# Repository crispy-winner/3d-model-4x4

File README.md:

# Macro Pad 4x4

В данном репозитории разведена печатная плата на основе микроконтроллера
[STM32F103CBT6](https://aliexpress.ru/popular/stm32f103cbt6.html) с USB Type-C.

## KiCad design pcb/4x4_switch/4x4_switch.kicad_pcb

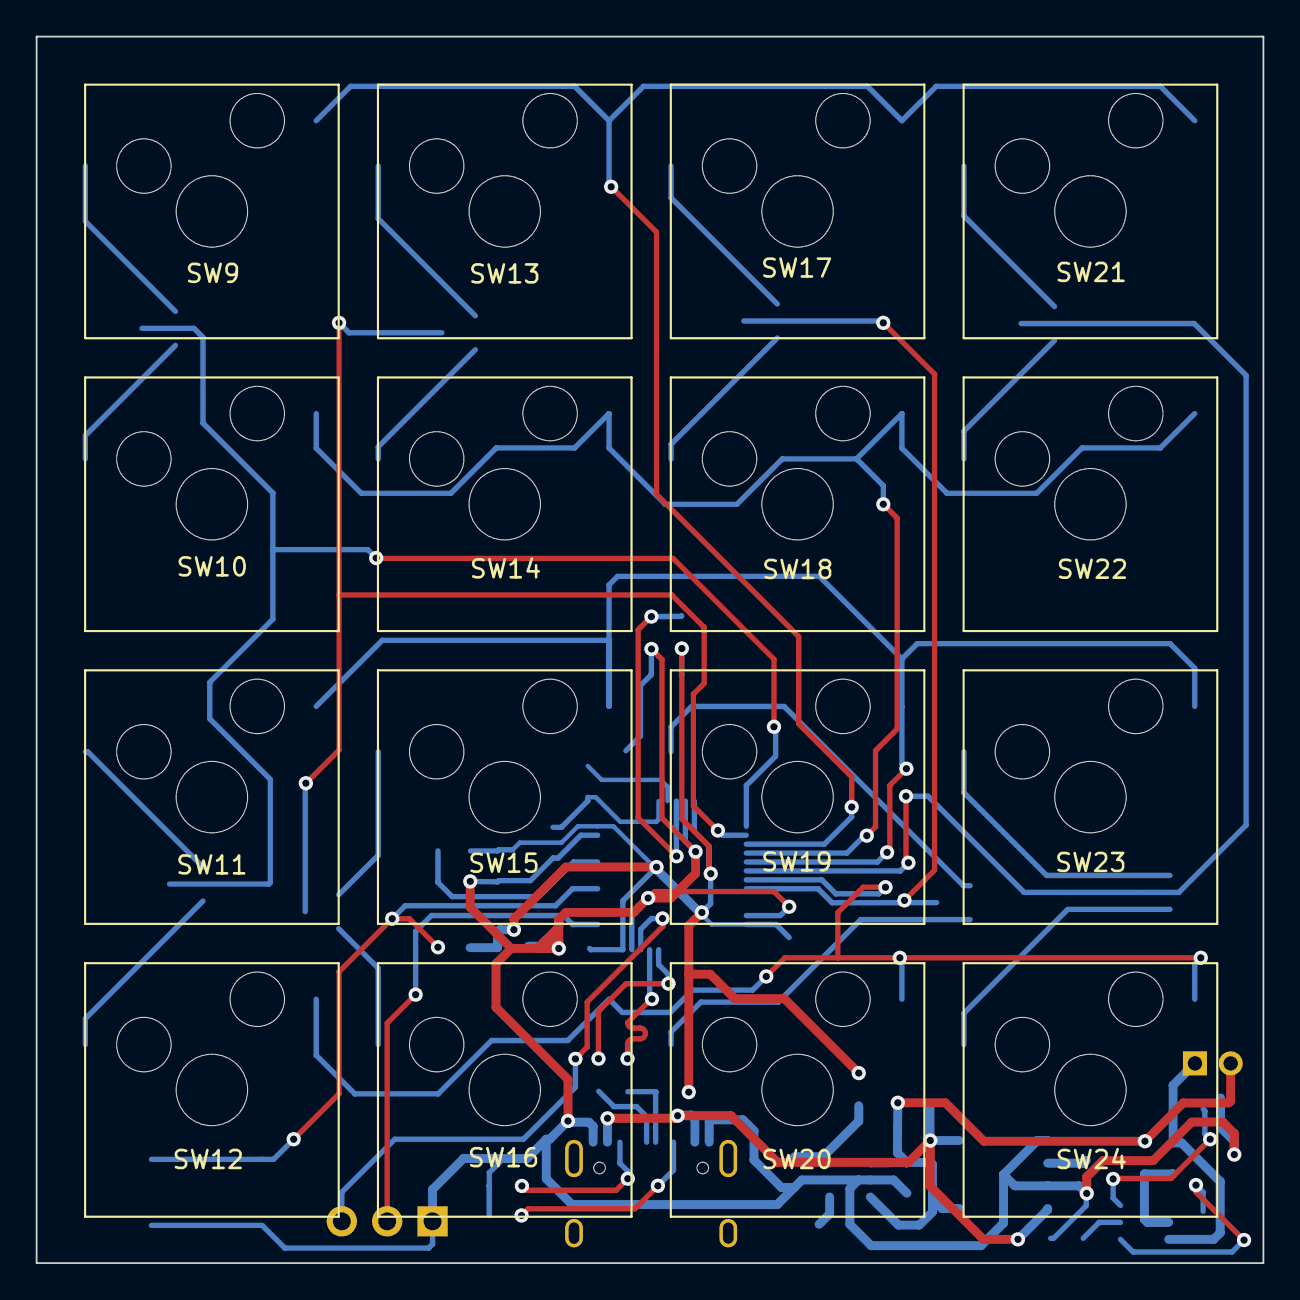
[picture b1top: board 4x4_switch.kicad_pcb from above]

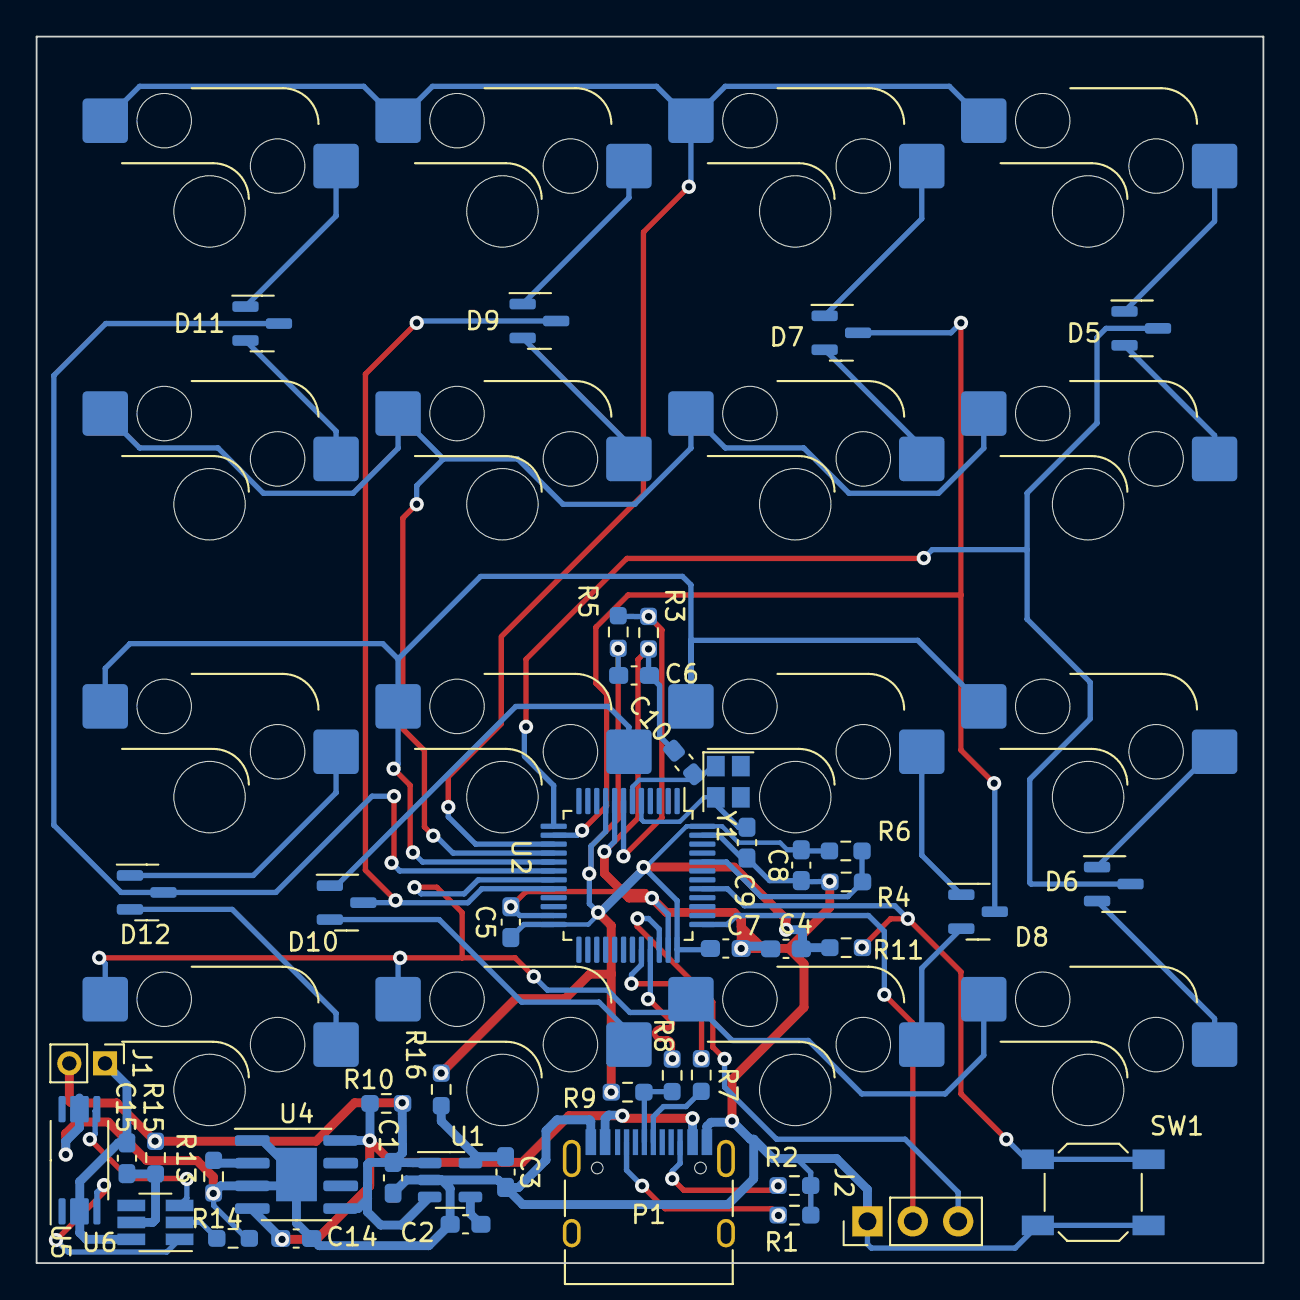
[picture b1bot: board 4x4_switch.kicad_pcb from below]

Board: 2 copper layers, 68.7 x 68.7 mm, 61 parts (45 on the bottom side), 49 nets.

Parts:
C1, C3: 1mkF; C_0603_1608Metric_Pad1.08x0.95mm_HandSolder
C2: byp10nF; C_0603_1608Metric_Pad1.08x0.95mm_HandSolder
C4: 10mkF; C_0603_1608Metric_Pad1.08x0.95mm_HandSolder
C5, C6, C7, C8, C14, C15: 100nF; C_0603_1608Metric_Pad1.08x0.95mm_HandSolder
C9, C10: 20pF; C_0603_1608Metric_Pad1.08x0.95mm_HandSolder
D5, D6, D7, D8, D9, D10, D11, D12: BAT54C; SOT-23
J1: Conn_01x02; PinHeader_1x02_P2.00mm_Vertical
J2: Conn_01x03; PinHeader_1x03_P2.54mm_Vertical
P1: USB_C_Plug_USB2.0; USB_C_Receptacle_HRO_TYPE-C-31-M-12
R1, R2: 5.1k; R_0603_1608Metric_Pad0.98x0.95mm_HandSolder
R3, R4: 100k; R_0603_1608Metric_Pad0.98x0.95mm_HandSolder
R5, R6, R11: 10k; R_0603_1608Metric_Pad0.98x0.95mm_HandSolder
R7, R8: 20R; R_0603_1608Metric_Pad0.98x0.95mm_HandSolder
R9, R14: 1k; R_0603_1608Metric_Pad0.98x0.95mm_HandSolder
R10, R16: 0; R_0603_1608Metric_Pad0.98x0.95mm_HandSolder
R13: 1.2k; R_0603_1608Metric_Pad0.98x0.95mm_HandSolder
R15: 100; R_0603_1608Metric_Pad0.98x0.95mm_HandSolder
SW1: SW_DIP_x01; SW_SPST_SKQG_WithoutStem
SW9, SW10, SW11, SW12, SW13, SW14, SW15, SW16, SW17, SW18, SW19, SW20, SW21, SW22, SW23, SW24: SW_DIP_x01; SW_Hotswap_Kailh_MX_1.00u
U1: LD3985M33R_SOT23; SOT-23-5
U2: STM32F103C8Tx; LQFP-48_7x7mm_P0.5mm
U4: TP4056; SOIC-8-1EP_3.9x4.9mm_P1.27mm_EP2.29x3mm
U5: FS8205A; TSSOP-8_4.4x3mm_P0.65mm
U6: DW01; SOT-23-6_Handsoldering
Y1: Crystal; Crystal_SMD_2520-4Pin_2.5x2.0mm

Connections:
+3.3V: C4.1, C5.1, C6.1, C7.1, C8.1, R5.1, R6.1, R9.2, R11.1, R16.2, U2.9 (VDDA), U2.24 (VDD), U2.36 (VDD), U2.48 (VDD)
+5V: C14.1, P1.A4 (VBUS), P1.A9 (VBUS), P1.B4 (VBUS), P1.B9 (VBUS), R10.2, U4.4 (VCC), U4.8 (CE)
+BATT: C1.1, J1.2, R10.1, R15.1, U1.1 (VIN), U1.3 (INH), U4.5 (BAT)
-BATT: C15.2, J1.1, U5.2 (Source_1), U5.3 (Source_1), U6.6 (GND)
BOOT0: R4.2, R6.2, U2.44 (BOOT0)
GND: C1.2, C2.2, C3.2, C4.2, C5.2, C6.2, C7.2, C8.2, C9.2, C10.2, C14.2, J2.1, P1.A1 (GND), P1.A12 (GND), P1.B1 (GND), P1.B12 (GND), R1.1, R2.1, R3.1, R4.1, R13.1, R14.1, SW1.1, U1.2 (GND), U2.8 (VSSA), U2.23 (VSS), U2.35 (VSS), U2.47 (VSS), U4.1 (TEMP), U4.3 (GND), U4.9 (PP), U5.6 (Source_2), U5.7 (Source_2)
unnamed: D5.1, SW9.1
unnamed: D5.2, SW10.1
unnamed: D6.1, SW11.1
unnamed: D6.2, SW12.1
unnamed: D7.1, SW13.1
unnamed: D7.2, SW14.1
unnamed: D8.1, SW15.1
unnamed: D8.2, SW16.1
unnamed: D9.1, SW17.1
unnamed: D9.2, SW18.1
unnamed: D10.1, SW19.1
unnamed: D10.2, SW20.1
unnamed: D11.1, SW21.1
unnamed: D11.2, SW22.1
unnamed: D12.1, SW23.1
unnamed: D12.2, SW24.1
unnamed: P1.A5 (CC), R1.2
unnamed: P1.A6 (D+), R8.2, R9.1
unnamed: P1.A7 (D-), R7.2
unnamed: P1.B5 (VCONN), R2.2
unnamed: C2.1, U1.4 (BYP)
unnamed: C3.1, R16.1, U1.5 (VOUT)
unnamed: R11.2, SW1.2, U2.41 (PB5)
unnamed: R13.2, U4.2 (PROG)
unnamed: U5.4 (Gate_1), U6.1 (OD)
unnamed: U5.5 (Gate_2), U6.3 (OC)
unnamed: R14.2, U6.2 (CS)
unnamed: C15.1, R15.2, U6.5 (VCC)
RESET: R3.2, R5.2, U2.7 (NRST)
SWCLK: J2.2, U2.37 (PA14)
SWDIO: J2.3, U2.34 (PA13)
USB_D+: R8.1, U2.33 (PA12)
USB_D-: R7.1, U2.32 (PA11)
col_1: D5.3, D6.3, U2.13 (PA3)
col_2: D7.3, D8.3, U2.14 (PA4)
col_3: D9.3, D10.3, U2.20 (PB2)
col_4: D11.3, D12.3, U2.18 (PB0)
osc1: C9.1, U2.5 (PD0), Y1.2
osc2: C10.1, U2.6 (PD1), Y1.1
row_1: SW9.2, SW13.2, SW17.2, SW21.2, U2.15 (PA5)
row_2: SW10.2, SW14.2, SW18.2, SW22.2, U2.16 (PA6)
row_3: SW11.2, SW15.2, SW19.2, SW23.2, U2.17 (PA7)
row_4: SW12.2, SW16.2, SW20.2, SW24.2, U2.19 (PB1)

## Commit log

2023-10-13 Создан файл README.md
